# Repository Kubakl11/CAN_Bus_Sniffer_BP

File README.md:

# CAN Bus Sniffer — Bachelor Thesis - Jakub Klášterka

> **Design and Implementation of a System for CAN Bus Data Analysis in Automotive Monitoring**
>
> Czech Technical University in Prague · Faculty of Electrical Engineering · 2026

---

## About

This project implements a **complete vehicle telemetry pipeline** — from reading OBD-II data off the car's CAN bus, through cellular transmission, to a live web dashboard.

```
   Vehicle CAN Bus (500 kbit/s)
       │
       ▼  OBD-II
  ┌─────────────────────────┐
  │  ESP32-S3 + MCP2518FD   │  ← Custom 4-layer PCB
  │  + A7670E LTE/GPS       │
  └────────┬────────────────┘
           │  HTTPS (LTE)
           ▼
  ┌─────────────────────────┐
  │  Flask Backend           │  ← Railway.app
  │  (REST API + SQLite)     │
  └────────┬────────────────┘
           │  fetch() @ 5 Hz
           ▼
  ┌─────────────────────────┐
  │  Web Dashboard           │  ← Chart.js + Leaflet
  │  (Vanilla HTML/CSS/JS)   │
  └─────────────────────────┘
```

---

## Hardware

| Component | Role |
|---|---|
| **ESP32-S3-MINI-1-N8** | Main MCU (dual-core, 240 MHz) |
| **MCP2518FD** | CAN controller (SPI, CAN 2.0B @ 500 kbit/s) |
| **ATA6563** | CAN transceiver (3.3 V logic / 5 V bus) |
| **SIMCom A7670E** | LTE Cat 1 modem + GNSS (GPS/GLONASS) |

PCB designed in **KiCad**,

---

## Firmware
- **CAN library:** ACAN2517FD
- **OBD-II:** PID discovery (SCAN) + cyclic reading (LOOP) at 150 ms
- **LTE:** AT command driver for A7670E — HTTPS POST with Bearer token + nonce
- **GPS:** NMEA parsing via `AT+CGNSSINFO`
- **WiFi:** SoftAP + captive portal for local configuration

## Backend

Flask app deployed on **Railway.app**.

| Endpoint | Method | Description |
|---|---|---|
| `/data` | `POST` | ESP sends OBD-II JSON (Bearer + nonce auth) |
| `/data` | `GET` | Dashboard reads latest telemetry |
| `/command` | `POST` | Queue command for ESP (SCAN / LOOP / STOP) |

**Security:** HTTPS · Bearer token · nonce replay protection

---

## Dashboard
Written using **HTML / CSS / JavaScript**

| Page | What it shows |
|---|---|
|  `dashboard.html` | Cockpit — gauges (RPM, speed), mini charts, alarms |
|  `vehicle-data.html` | Full PID table with live values |
|  `graphs.html` | Time-series charts (Chart.js) |
|  `alarms.html` | Configurable alarm thresholds |
|  `consumption.html` | Fuel consumption analytics |
|  `map.html` | Live GPS track (Leaflet + Mapbox) |
|  `diagnostic.html` | CAN frame builder, live monitor, UDS, serial console |

**Design:** Dark theme (navy + blue accent), JetBrains Mono for numerics, responsive layout.

`data.js` serves as the **single integration point** 

---

## Quick Start

```bash
# Firmware (PlatformIO)
pio run -e obd_reader -t upload
pio device monitor

# Backend (local)
pip install -r requirements.txt
flask run

# Dashboard
# Open dashboard.html with Live Server
```

---

## 📝 Thesis

Written in **LaTeX** using the `ctuthesis` template. The thesis covers a review of automotive communication buses (CAN, LIN, FlexRay, Ethernet), the OBD-II diagnostic standard, hardware design, firmware implementation, server architecture, and the web dashboard.

---

<p align="center">
  <sub>Jakub Klášterka · CTU FEE Prague · 2026</sub>
</p>

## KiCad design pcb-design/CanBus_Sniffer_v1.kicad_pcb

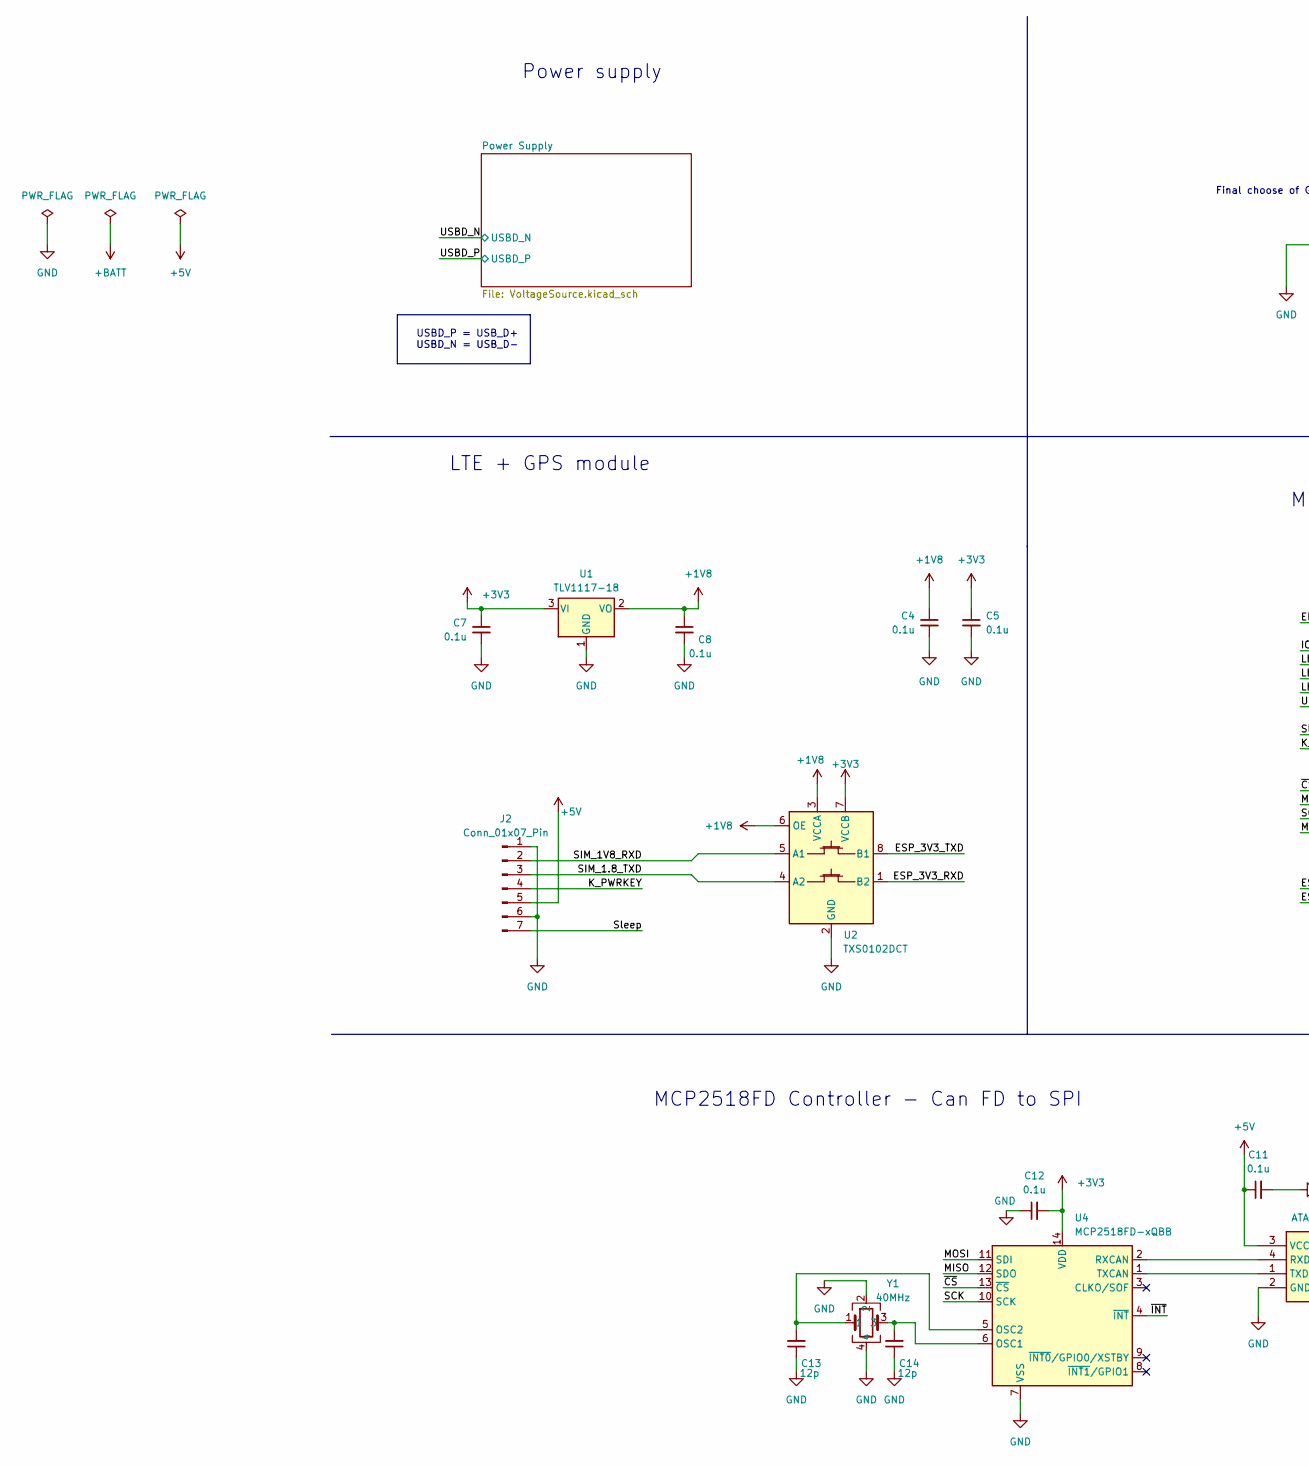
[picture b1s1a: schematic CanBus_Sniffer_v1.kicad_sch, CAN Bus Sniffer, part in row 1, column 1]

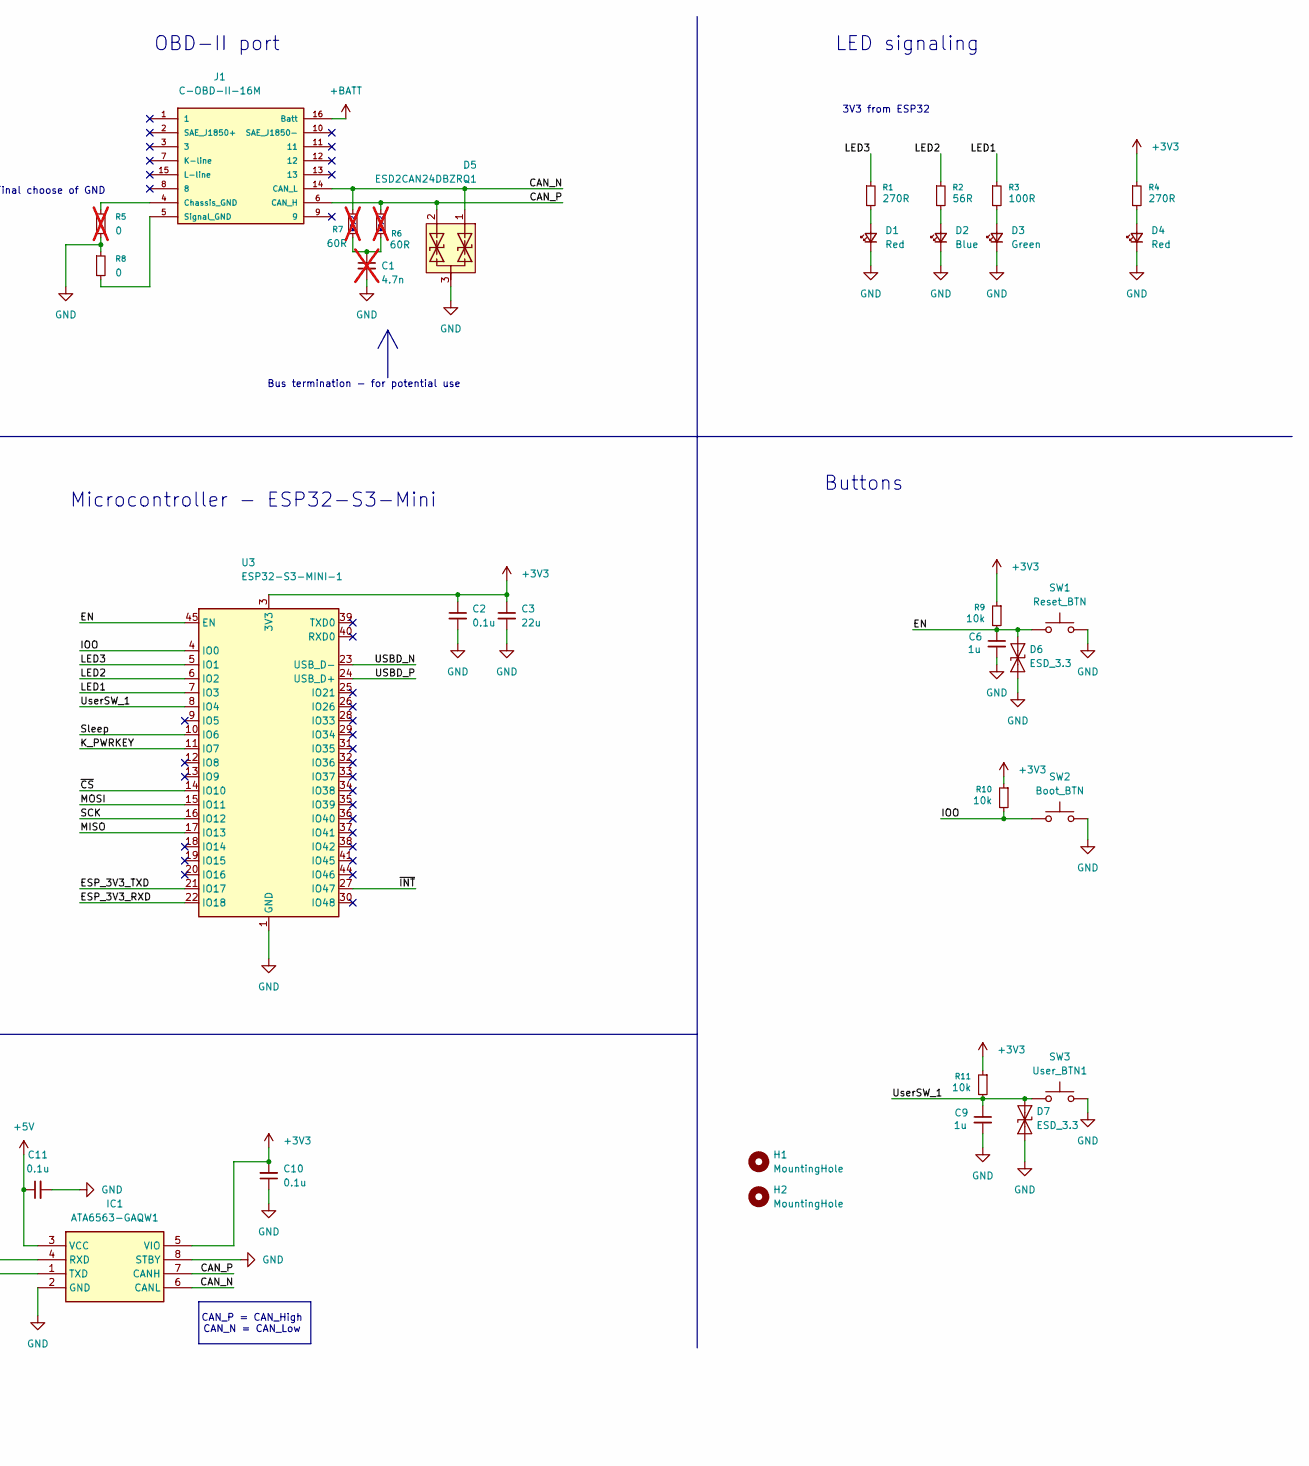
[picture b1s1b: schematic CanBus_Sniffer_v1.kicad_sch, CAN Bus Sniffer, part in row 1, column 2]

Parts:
C1: 4.7n; C_0603_1608Metric; not fitted
C2: 0.1u; C_0603_1608Metric_Pad1.08x0.95mm_HandSolder; Mouser 187-CL31B106KAHNNNE
C3: 22u; C_1206_3216Metric_Pad1.33x1.80mm_HandSolder; Mouser No 963-MSASE31LBB7226MT
C4, C5, C7, C8, C10, C11, C12: 0.1u; C_0603_1608Metric_Pad1.08x0.95mm_HandSolder; Mouser 80-C1206C104J5RAC
C6, C9: 1u; C_0603_1608Metric_Pad1.08x0.95mm_HandSolder; Mouser No 187-CL10A105KO8NNNL
C13, C14: 12p; C_0603_1608Metric_Pad1.08x0.95mm_HandSolder; Mouser 80-C1206C104J5RAC
D1, D4: Red; LED_0603_1608Metric_Pad1.05x0.95mm_HandSolder; Mouser No 710-150060RS75003
D2: Blue; LED_0603_1608Metric_Pad1.05x0.95mm_HandSolder; Mouser No 743-S63BT5B
D3: Green; LED_0603_1608Metric_Pad1.05x0.95mm_HandSolder; Mouser No 78-VLMTG1400-GS08
D5: ESD2CAN24DBZRQ1; TSOT-23; Mouser Part Number 595-ESD2CAN24DBZRQ1
D6, D7: ESD_3.3; D_SOD-323; Mouser No 621-D5V0L1B2WS-7
H1, H2: MountingHole; MountingHole_2.1mm
IC1: ATA6563-GAQW1; SOIC127P600X175-8N; Mouser Part Number 579-ATA6563-GAQW1
J1: C-OBD-II-16M; COMTECH_C-OBD-II-16M; PARTREV A
J2: Conn_01x07_Pin; PinHeader_1x07_P2.54mm_Vertical; Mouser No 737-RS1-07-G
R1, R4: 270R; R_0603_1608Metric_Pad0.98x0.95mm_HandSolder; Mouser 603-RE1206DRE071KL
R2: 56R; R_0603_1608Metric_Pad0.98x0.95mm_HandSolder; Mouser 603-RE1206DRE071KL
R3: 100R; R_0603_1608Metric_Pad0.98x0.95mm_HandSolder; Mouser 603-RE1206DRE071KL
R5: 0; R_1206_3216Metric_Pad1.30x1.75mm_HandSolder; Mouser No 71-RCS12060000Z0EA; not fitted
R6, R7: 60R; R_0603_1608Metric_Pad0.98x0.95mm_HandSolder; not fitted
R8: 0; R_1206_3216Metric_Pad1.30x1.75mm_HandSolder; Mouser No 71-RCS12060000Z0EA
R9, R10, R11: 10k; R_0603_1608Metric_Pad0.98x0.95mm_HandSolder; Mouser 603-AC1206FR-7W10KL
SW1: Reset_BTN; SW_SPST_TL1017; Mouser No 612-TL1017AAAF260QG
SW2: Boot_BTN; SW_SPST_TL1017; Mouser No 612-TL1017AAAF260QG
SW3: User_BTN1; SW_SPST_EVQP2_ShortPushTravel_H2.5mm; Mouser No 667-EVQ-PUJ02K
U1: TLV1117-18; SOT-223-3_TabPin2; Mouser No 595-TLV1117LV18DCYR
U2: TXS0102DCT; SSOP-8_2.95x2.8mm_P0.65mm; Mouser No 595-TXS0102VDCTR
U3: ESP32-S3-MINI-1; ESP32-S2-MINI-1; Mouser No 356-ESP32-S3-MINI1N8
U4: MCP2518FD-xQBB; SOIC127P600X175-14N; Mouser No 579-MCP2518FDT-E/SL
Y1: 40MHz; Crystal_SMD_2016-4Pin_2.0x1.6mm; Mouser No 815-11W40-8D1XT

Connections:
+1V8: C4.1, C8.1, U1.2 (VO), U2.3 (VCCA), U2.6 (OE)
+3V3: C2.1, C3.1, C5.1, C7.1, C10.2, C12.2, IC1.5 (VIO), R4.1, R9.1, R10.1, R11.1, U1.3 (VI), U2.7 (VCCB), U3.3 (3V3), U4.14 (VDD); also elsewhere on the board
+5V: C11.1, IC1.3 (VCC), J2.5; also elsewhere on the board
+BATT: J1.16 (Batt); also elsewhere on the board
/CAN_N: D5.1, IC1.6 (CANL), J1.14 (CAN_L), R6.1
/CAN_P: D5.2, IC1.7 (CANH), J1.6 (CAN_H), R7.1
/EN: C6.1, D6.2 (A2), R9.2, SW1.1, U3.45 (EN)
/ESP_3V3_RXD: U2.1 (B2), U3.22 (IO18)
/ESP_3V3_TXD: U2.8 (B1), U3.21 (IO17)
/IOO: R10.2, SW2.1, U3.4 (IO0)
/K_PWRKEY: J2.4, U3.11 (IO7)
/LED1: R3.1, U3.7 (IO3)
/LED2: R2.1, U3.6 (IO2)
/LED3: R1.1, U3.5 (IO1)
/MISO: U3.17 (IO13), U4.12 (SDO)
/MOSI: U3.15 (IO11), U4.11 (SDI)
/SCK: U3.16 (IO12), U4.10 (SCK)
/SIM_1.8_TXD: J2.3, U2.4 (A2)
/SIM_1V8_RXD: J2.2, U2.5 (A1)
/Sleep: J2.7, U3.10 (IO6)
/USBD_N: U3.23 (USB_D-); also elsewhere on the board
/USBD_P: U3.24 (USB_D+); also elsewhere on the board
/UserSW_1: C9.1, D7.2 (A2), R11.2, SW3.1, U3.8 (IO4)
/~CS: U3.14 (IO10), U4.13 (~CS)
/~INT: U3.27 (IO47), U4.4 (~INT)
GND: C1.2, C2.2, C3.2, C4.2, C5.2, C6.2, C7.2, C8.2, C9.2, C10.1, C11.2, C12.1, C13.1, C14.1, D1.1 (K), D2.1 (K), D3.1 (K), D4.1 (K), D5.3, D6.1 (A1), D7.1 (A1), IC1.2 (GND), IC1.8 (STBY), J2.1, J2.6, R5.2, R8.1, SW1.2, SW2.2, SW3.2, U1.1 (GND), U2.2 (GND), U3.1 (GND), U3.2 (GND), U3.42 (GND), U3.43 (GND), U3.46 (GND), U3.47 (GND), U3.48 (GND), U3.49 (GND), U3.50 (GND), U3.51 (GND), U3.52 (GND), U3.53 (GND), U3.54 (GND), U3.55 (GND), U3.56 (GND), U3.57 (GND), U3.58 (GND), U3.59 (GND), U3.60 (GND), U3.61 (GND), U3.62 (GND), U3.63 (GND), U3.64 (GND), U3.65 (GND), U4.7 (VSS), Y1.2, Y1.4; also elsewhere on the board
unnamed: C1.1, R6.2, R7.2
unnamed: D1.2 (A), R1.2
unnamed: D2.2 (A), R2.2
unnamed: D3.2 (A), R3.2
unnamed: D4.2 (A), R4.2
unnamed: IC1.4 (RXD), U4.2 (RXCAN)
unnamed: IC1.1 (TXD), U4.1 (TXCAN)
unnamed: J1.4 (Chassis_GND), R5.1
unnamed: J1.5 (Signal_GND), R8.2
unnamed: C14.2, U4.6 (OSC1), Y1.3
unnamed: C13.2, U4.5 (OSC2), Y1.1

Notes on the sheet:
RT/2
USBD_P = USB_D+ USBD_N = USB_D-
LTE + GPS module
OBD-II port
Microcontroller - ESP32-S3-Mini
3V3 from ESP32
Final choose of GND
Bus termination - for potential use
Power supply
MCP2518FD Controller - Can FD to SPI
Buttons
LED signaling
CAN_P = CAN_High CAN_N = CAN_Low

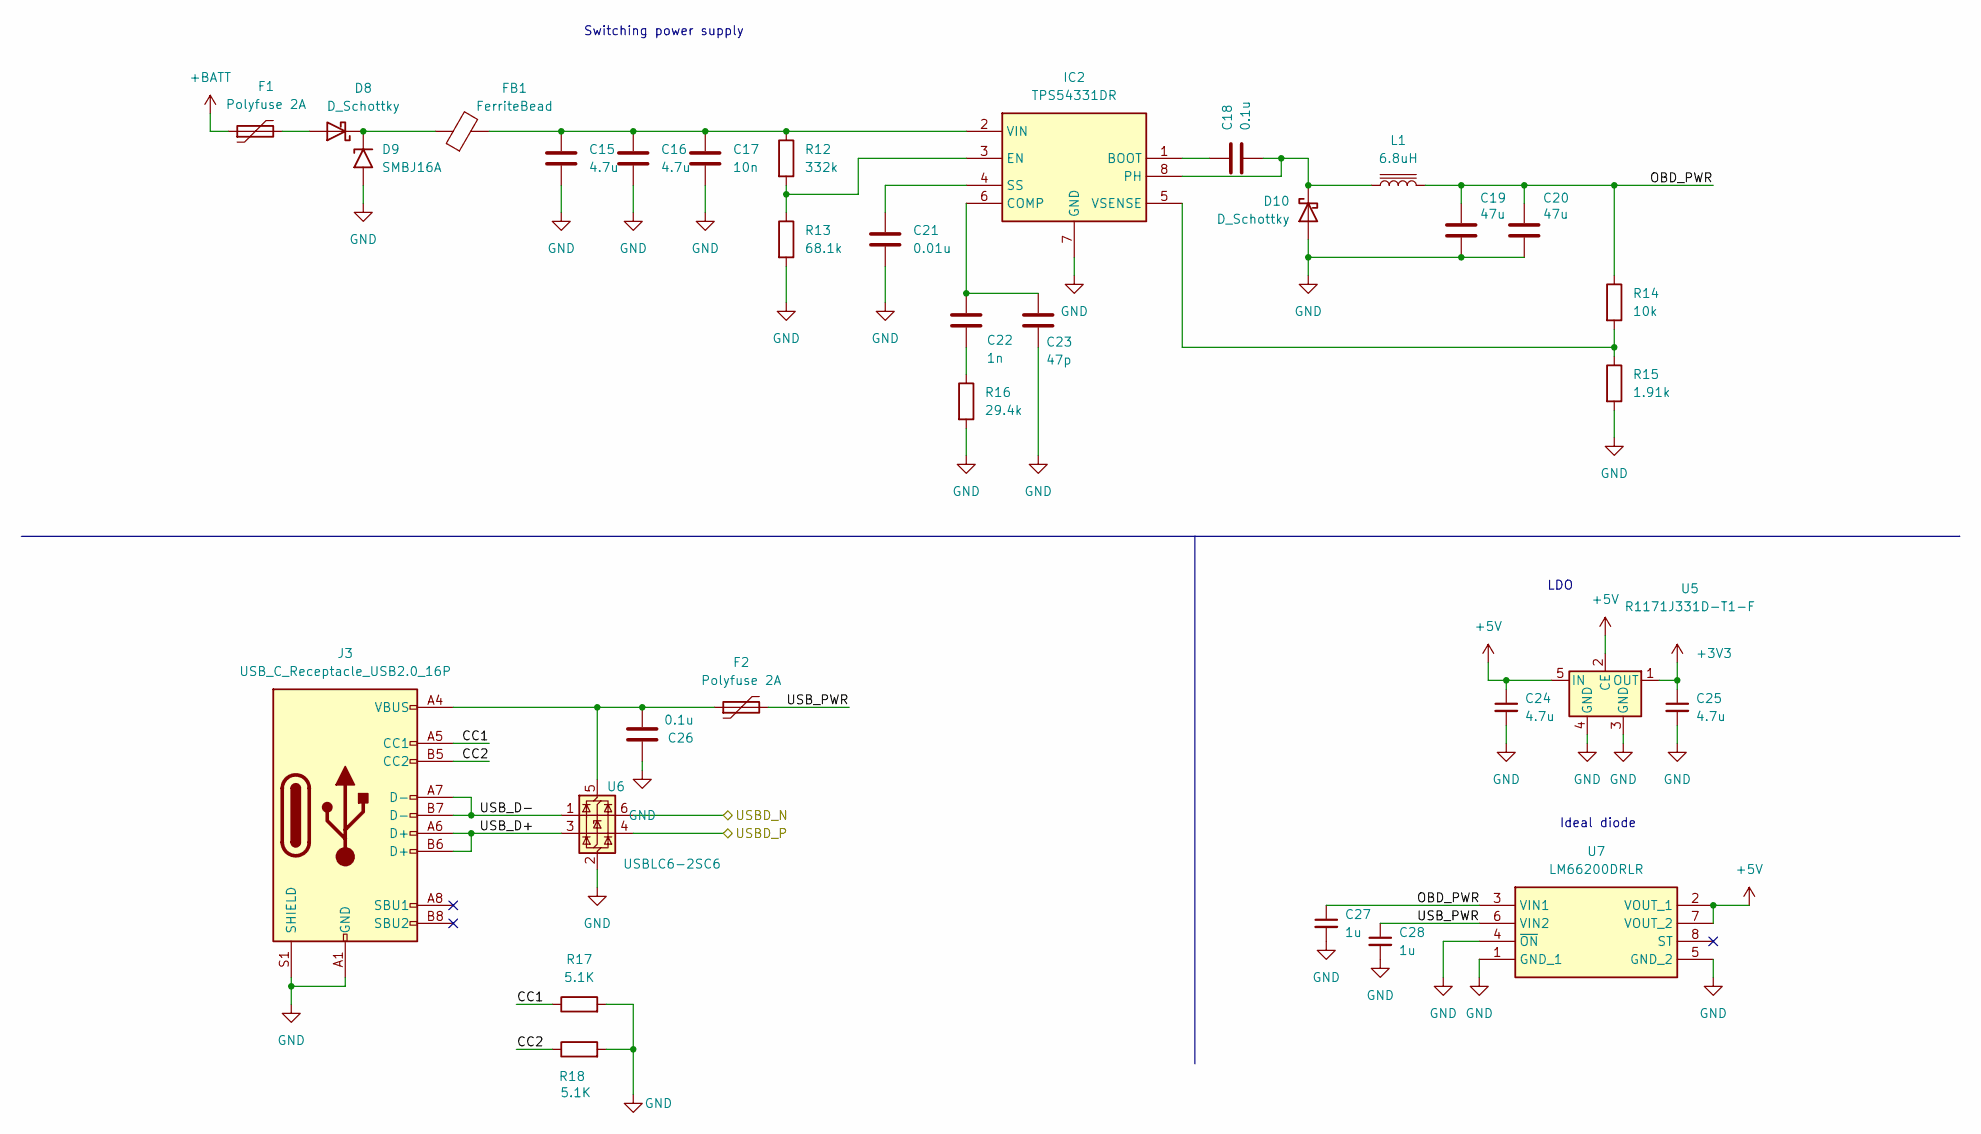
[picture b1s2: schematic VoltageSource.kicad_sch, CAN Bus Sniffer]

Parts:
C15, C16: 4.7u; R_0805_2012Metric_Pad1.20x1.40mm_HandSolder; Mouser No 810-CGA4J1X7R1H475K1
C17: 10n; C_0603_1608Metric_Pad1.08x0.95mm_HandSolder; Mouser No 810-CGA3E2X7R1H103K
C18: 0.1u; C_0603_1608Metric_Pad1.08x0.95mm_HandSolder; Mouser No 603-CC603KRX7R8BB104
C19, C20: 47u; R_1206_3216Metric_Pad1.30x1.75mm_HandSolder; Mouser No 963-MSASE31LBB5476MT
C21: 0.01u; C_0603_1608Metric_Pad1.08x0.95mm_HandSolder; Mouser No 810-CGA3E2X7R1H103K
C22: 1n; C_0603_1608Metric_Pad1.08x0.95mm_HandSolder; Mouser No 603-AC603KRX7R8BB102
C23: 47p; C_0603_1608Metric_Pad1.08x0.95mm_HandSolder; Mouser No 77-VJ0603A470JXXPBC
C24, C25: 4.7u; C_0603_1608Metric_Pad1.08x0.95mm_HandSolder; Mouser No 81-GRM188Z71C475KE1D
C26: 0.1u; C_0603_1608Metric_Pad1.08x0.95mm_HandSolder; Mouser No 810-C1608X7R1E104M
C27, C28: 1u; C_0603_1608Metric_Pad1.08x0.95mm_HandSolder; Mouser No 791-0603B105K160CT
D8: D_Schottky; D_SMA; Mouser No 750-SS54F-HF
D9: SMBJ16A; D_SMB; Mouser No 576-SMBJ16A
D10: D_Schottky; D_SMA; Mouser No 621-B340AE-13
F1: Polyfuse 2A; Fuse_1812_4532Metric_Pad1.30x3.40mm_HandSolder; Mouser No 603-SMD1812B200TF/30
F2: Polyfuse 2A; R_1210_3225Metric_Pad1.30x2.65mm_HandSolder; Mouser 576-1210L200PR
FB1: FerriteBead; L_0805_2012Metric_Pad1.05x1.20mm_HandSolder; Mouser No 81-BLM21PG121SN1D
IC2: TPS54331DR; SOIC-8-1EP_3.9x4.9mm_P1.27mm_EP2.29x3mm; Mouser Part Number 595-TPS54331DR
J3: USB_C_Receptacle_USB2.0_16P; USB_C_Receptacle_GCT_USB4105-xx-A_16P_TopMnt_Horizontal; Mouser 640-USB4105-GF-A-120
L1: 6.8uH; L_6.3x6.3_H3; Mouser No 810-VLS6045EX-6R8M
R12: 332k; R_0603_1608Metric_Pad0.98x0.95mm_HandSolder; Mouser No 667-ERJ-PA3F3323V
R13: 68.1k; R_0603_1608Metric_Pad0.98x0.95mm_HandSolder; Mouser No 755-ESR03EZPF6812
R14: 10k; R_0603_1608Metric_Pad0.98x0.95mm_HandSolder; Mouser No 71-CRCW060310K0FKEE
R15: 1.91k; R_0603_1608Metric_Pad0.98x0.95mm_HandSolder; Mouser No 71-CRCW0603-1.91K-E3
R16: 29.4k; R_0603_1608Metric_Pad0.98x0.95mm_HandSolder; Mouser No 71-CRCW060329K4FKEAH
R17, R18: 5.1K; R_0603_1608Metric_Pad0.98x0.95mm_HandSolder; Mouser 71-CRCW1206-5.1K-E3
U5: R1171J331D-T1-F; TO-252-5_TabPin3; Mouser No 848-R1171J331DT1F
U6: USBLC6-2SC6; SOT-23-6; Mouser 511-USBLC6-2SC6
U7: LM66200DRLR; SOTFL50P160X60-8N; Mouser Part Number 595-LM66200DRLR

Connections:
+3V3: C25.1, U5.1 (OUT); also elsewhere on the board
+5V: C24.1, U5.2 (CE), U5.5 (IN), U7.2 (VOUT_1), U7.7 (VOUT_2); also elsewhere on the board
+BATT: F1.1; also elsewhere on the board
/Power Supply/CC1: J3.A5 (CC1), R17.1
/Power Supply/CC2: J3.B5 (CC2), R18.1
/Power Supply/OBD_PWR: C19.1, C20.1, C27.1, L1.2, R14.1, U7.3 (VIN1)
/Power Supply/USB_D+: J3.A6 (D+), J3.B6 (D+), U6.3 (I/O2)
/Power Supply/USB_D-: J3.A7 (D-), J3.B7 (D-), U6.1 (I/O1)
/Power Supply/USB_PWR: C28.1, F2.2, U7.6 (VIN2)
/USBD_N: U6.6 (I/O1); also elsewhere on the board
/USBD_P: U6.4 (I/O2); also elsewhere on the board
GND: C15.2, C16.2, C17.2, C19.2, C20.2, C21.2, C23.2, C24.2, C25.2, C26.2, C27.2, C28.2, D9.2 (A2), D10.2 (A), IC2.7 (GND), IC2.9 (GND), J3.A1 (GND), J3.A12 (GND), J3.B1 (GND), J3.B12 (GND), J3.S1 (SHIELD), R13.2, R15.2, R16.2, R17.2, R18.2, U5.3 (GND), U5.4 (GND), U6.2 (GND), U7.1 (GND_1), U7.4 (~ON), U7.5 (GND_2); also elsewhere on the board
unnamed: C22.2, R16.1
unnamed: D8.2 (A), F1.2
unnamed: D8.1 (K), D9.1 (A1), FB1.1
unnamed: C18.1, D10.1 (K), IC2.8 (PH), L1.1
unnamed: C18.2, IC2.1 (BOOT)
unnamed: C22.1, C23.1, IC2.6 (COMP)
unnamed: IC2.3 (EN), R12.2, R13.1
unnamed: C21.1, IC2.4 (SS)
unnamed: C15.1, C16.1, C17.1, FB1.2, IC2.2 (VIN), R12.1
unnamed: IC2.5 (VSENSE), R14.2, R15.1
unnamed: C26.1, F2.1, J3.A4 (VBUS), J3.A9 (VBUS), J3.B4 (VBUS), J3.B9 (VBUS), U6.5 (VBUS)

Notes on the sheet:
Ideal diode
Switching power supply
LDO

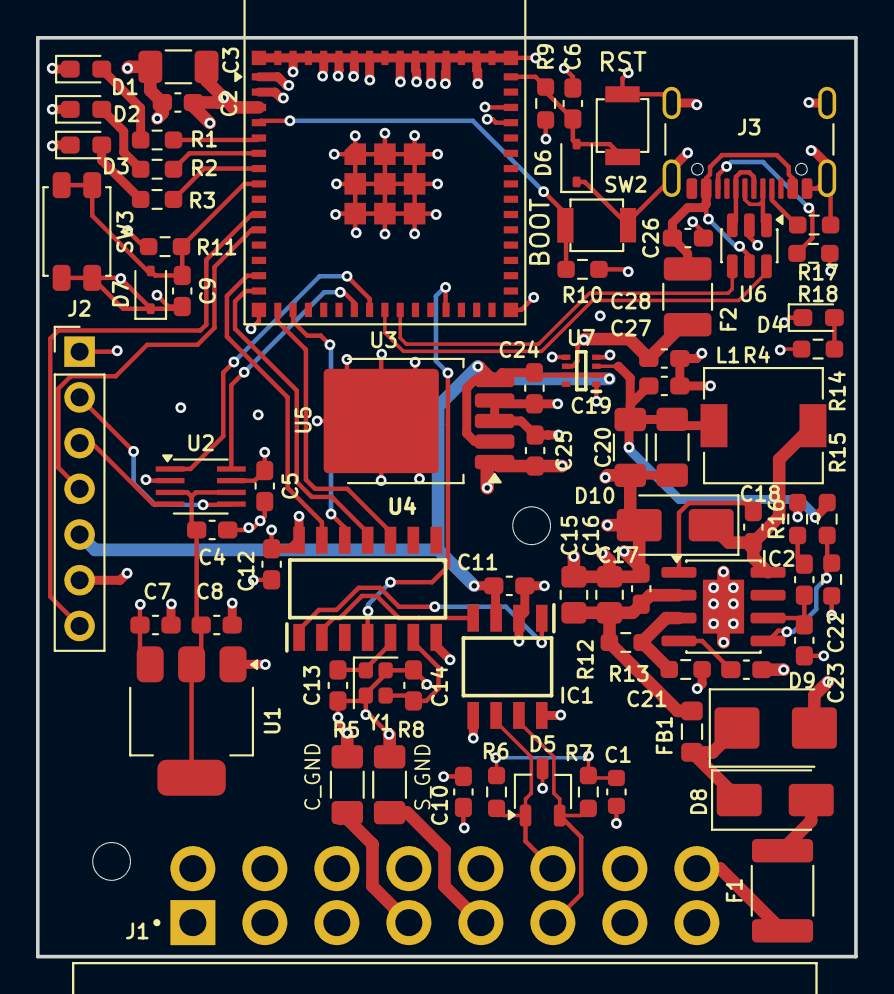
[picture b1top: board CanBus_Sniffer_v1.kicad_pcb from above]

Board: 4 copper layers, 45.5 x 51.0 mm, 78 parts (0 on the bottom side), 54 nets.

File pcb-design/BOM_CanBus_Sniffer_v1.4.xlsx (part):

Reference | Qty | Value | DNP | Exclude from BOM | Exclude from Board | Footprint | Datasheet | Mouser No | Mouser Part Number | Place | Note
Y1 | 1 | 40MHz |  |  |  | Crystal:Crystal_SMD_2016-4Pin_2.0x1.6mm | https://eu.mouser.com/datasheet/3/184/1/ABM11W.pdf | 815-11W40-8D1XT |  | YES
U7 | 1 | LM66200DRLR |  |  |  | Soucastky:SOTFL50P160X60-8N | https://www.ti.com/lit/ds/symlink/lm66200.pdf?ts=17723632276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 | 595-LM66200DRLR | 595-LM66200DRLR | YES
U6 | 1 | USBLC6-2SC6 |  |  |  | Package_TO_SOT_SMD:SOT-23-6 | https://www.st.com/resource/en/datasheet/usblc6-2.pdf | 511-USBLC6-2SC6 |  | YES
U5 | 1 | R1171J331D-T1-F |  |  |  | Package_TO_SOT_SMD:TO-252-5_TabPin3 | https://www.nisshinbo-microdevices.co.jp/en/pdf/datasheet/r1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 | 848-R1171J331DT1F |  | YES
U4 | 1 | MCP2518FD-xQBB |  |  |  | Soucastky:SOIC127P600X175-14N | https://cz.mouser.com/datasheet/3/282/1/External-CAN-FD-Cont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 | 579-MCP2518FDT-E/SL |  | YES
U3 | 1 | ESP32-S3-MINI-1 |  |  |  | RF_Module:ESP32-S2-MINI-1 | https://documentation.espressif.com/esp32-s3-mini-1_mini-1u_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 | 356-ESP32-S3-MINI1N8 |  | YES
U2 | 1 | TXS0102DCT |  |  |  | Package_SO:SSOP-8_2.95x2.8mm_P0.65mm | https://www.ti.com/lit/ds/symlink/txs0102v.pdf?ts=1771762179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 | 595-TXS0102VDCTR |  | YES
U1 | 1 | TLV1117-18 |  |  |  | Package_TO_SOT_SMD:SOT-223-3_TabPin2 | https://www.ti.com/lit/ds/symlink/tlv1117lv.pdf?ts=177181211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 | 595-TLV1117LV18DCYR |  | YES
SW3 | 1 | User_BTN1 |  |  |  | Button_Switch_SMD:SW_SPST_EVQP2_ShortPushTravel_H2.5mm | https://4donline.ihs.com/images/VipMasterIC/IC/PANA/PANA-S-A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 | 667-EVQ-PUJ02K |  | YES
SW2 | 1 | Boot_BTN |  |  |  | Button_Switch_SMD:SW_SPST_TL1017 | https://www.mouser.com/catalog/specsheets/E-Switch_TL1017.pd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 | 612-TL1017AAAF260QG |  | YES
SW1 | 1 | Reset_BTN |  |  |  | Button_Switch_SMD:SW_SPST_TL1017 | https://www.mouser.com/catalog/specsheets/E-Switch_TL1017.pd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 | 612-TL1017AAAF260QG |  | YES
R17,R18 | 2 | 5.1K |  |  |  | Resistor_SMD:R_0603_1608Metric_Pad0.98x0.95mm_HandSolder | ~ | 71-RCS06035K10FKEA |  | YES
R16 | 1 | 29.4k |  |  |  | Resistor_SMD:R_0603_1608Metric_Pad0.98x0.95mm_HandSolder | ~ | 71-CRCW060329K4FKEAH |  | YES
R15 | 1 | 1.91k |  |  |  | Resistor_SMD:R_0603_1608Metric_Pad0.98x0.95mm_HandSolder | ~ | 71-CRCW0603-1.91K-E3 |  | YES
R13 | 1 | 68.1k |  |  |  | Resistor_SMD:R_0603_1608Metric_Pad0.98x0.95mm_HandSolder | ~ | 755-ESR03EZPF6812 |  | YES
R12 | 1 | 332k |  |  |  | Resistor_SMD:R_0603_1608Metric_Pad0.98x0.95mm_HandSolder | ~ | 667-ERJ-PA3F3323V |  | YES
R9,R10,R11,R14 | 4 | 10k |  |  |  | Resistor_SMD:R_0603_1608Metric_Pad0.98x0.95mm_HandSolder | ~ | 71-CRCW060310K0FKEE |  | YES
R8 | 1 | 0R |  |  |  | Resistor_SMD:R_1206_3216Metric_Pad1.30x1.75mm_HandSolder | ~ | 71-RCS12060000Z0EA |  | YES
R6,R7 | 2 | 60R | DNP |  |  | Resistor_SMD:R_0603_1608Metric_Pad0.98x0.95mm_HandSolder | ~ | 72-P0603C60R0BNT |  | NO | Optional impedance matching
R5 | 1 | 0R | DNP |  |  | Resistor_SMD:R_1206_3216Metric_Pad1.30x1.75mm_HandSolder | ~ | 71-RCS12060000Z0EA |  | NO | Optional - Chassis GND
R3 | 1 | 100R |  |  |  | Resistor_SMD:R_0603_1608Metric_Pad0.98x0.95mm_HandSolder | ~ | 603-SR0603FR-7T100RL |  | YES
R2 | 1 | 56R |  |  |  | Resistor_SMD:R_0603_1608Metric_Pad0.98x0.95mm_HandSolder | ~ | 71-CRCW060356R0FKEAH |  | YES
R1,R4 | 2 | 270R |  |  |  | Resistor_SMD:R_0603_1608Metric_Pad0.98x0.95mm_HandSolder | ~ | 71-CRCW0603270RFKEAH |  | YES
L1 | 1 | 6.8uH |  |  |  | Inductor_SMD:L_6.3x6.3_H3 | https://product.tdk.com/system/files/dam/doc/product/inducto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 | 810-VLS6045EX-6R8M |  | YES
J3 | 1 | USB_C_Receptacle_USB2.0_16P |  |  |  | Connector_USB:USB_C_Receptacle_GCT_USB4105-xx-A_16P_TopMnt_Horizontal | https://www.mouser.com/catalog/specsheets/Global_Connector_T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 | 640-USB4105-GF-A-120 |  | YES
J2 | 1 | Conn_01x07_Pin |  |  |  | Connector_PinHeader_2.54mm:PinHeader_1x07_P2.54mm_Vertical | Headers & Wire Housings RECEPTACLE STRIP 7P 2.54MM PITCH | 737-RS1-07-G |  | YES
J1 | 1 | C-OBD-II-16M |  |  |  | Soucastky:COMTECH_C-OBD-II-16M |  |  |  | YES
IC2 | 1 | TPS54331DR |  |  |  | Package_SO:SOIC-8-1EP_3.9x4.9mm_P1.27mm_EP2.29x3mm | http://www.ti.com/lit/gpn/tps54331 | 595-TPS54331DR | 595-TPS54331DR | YES
IC1 | 1 | ATA6563-GAQW1 |  |  |  | Soucastky:SOIC127P600X175-8N | https://cz.mouser.com/datasheet/3/282/1/ATA6562.3-Data-Sheet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 | 579-ATA6563-GAQW1 | 579-ATA6563-GAQW1 | YES
H1,H2 | 2 | MountingHole |  | Excluded from BOM |  | MountingHole:MountingHole_2.1mm | ~ |  |  | YES
FB1 | 1 | FerriteBead |  |  |  | Inductor_SMD:L_0805_2012Metric_Pad1.05x1.20mm_HandSolder | https://eu.mouser.com/datasheet/3/76/1/ENFA0005.pdf | 81-BLM21PG121SN1D |  | YES
F2 | 1 | Polyfuse 2A |  |  |  | Resistor_SMD:R_1210_3225Metric_Pad1.30x2.65mm_HandSolder | https://www.littelfuse.com/assetdocs/1210l_datasheet_update.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 | 576-1210L200PR |  | YES
F1 | 1 | Polyfuse 2A |  |  |  | Fuse:Fuse_1812_4532Metric_Pad1.30x3.40mm_HandSolder | https://cz.mouser.com/datasheet/3/508/1/SMD1812_1.pdf | 603-SMD1812B200TF/30 |  | YES
D9 | 1 | SMBJ16A |  |  |  | Diode_SMD:D_SMB | https://www.littelfuse.com/assetdocs/tvs-diodes-smbj-series-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 | 576-SMBJ16A |  | YES
D8 | 1 | D_Schottky |  |  |  | Diode_SMD:D_SMA | https://cz.mouser.com/datasheet/3/819/1/20190806174558.pdf | 750-SS54F-HF |  | YES
D10 | 1 | D_Schottky |  |  |  | Diode_SMD:D_SMA | https://4donline.ihs.com/images/VipMasterIC/IC/DIOD/DIOD-S-A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 | 621-B340AE-13 |  | YES
D6,D7 | 2 | ESD_3.3 |  |  |  | Diode_SMD:D_SOD-323 | https://eu.mouser.com/datasheet/3/175/1/D5V0L1B2WS.pdf | 621-D5V0L1B2WS-7 |  | YES
D5 | 1 | ESD2CAN24DBZRQ1 |  |  |  | Package_TO_SOT_SMD:TSOT-23 | https://www.ti.com/lit/ds/symlink/esd2canxl24-q1.pdf?ts=1771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 | 595-ESD2CAN24DBZRQ1 | 595-ESD2CAN24DBZRQ1 | YES
D3 | 1 | Green |  |  |  | LED_SMD:LED_0603_1608Metric_Pad1.05x0.95mm_HandSolder | ~ | 78-VLMTG1400-GS08 |  | YES
D2 | 1 | Blue |  |  |  | LED_SMD:LED_0603_1608Metric_Pad1.05x0.95mm_HandSolder | ~ | 743-S63BT5B |  | YES
D1,D4 | 2 | Red |  |  |  | LED_SMD:LED_0603_1608Metric_Pad1.05x0.95mm_HandSolder | ~ | 710-150060RS75003 |  | YES
C24,C25 | 2 | 4.7u |  |  |  | Capacitor_SMD:C_0603_1608Metric_Pad1.08x0.95mm_HandSolder | https://pim.murata.com/asset/pim4/ceramicCapacitorSMD/GRM188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 | 81-GRM188Z71C475KE1D |  | YES
C23 | 1 | 47p |  |  |  | Capacitor_SMD:C_0603_1608Metric_Pad1.08x0.95mm_HandSolder | https://www.vishay.com/docs/28548/vjw1bcbascomseries.pdf | 77-VJ0603A470JXXPBC |  | YES
C22 | 1 | 1n |  |  |  | Capacitor_SMD:C_0603_1608Metric_Pad1.08x0.95mm_HandSolder | https://cz.mouser.com/datasheet/3/508/1/UPY-AC_NP0X7RX7S_6.3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 | 603-AC603KRX7R8BB102 |  | YES
C21 | 1 | 0.01u |  |  |  | Capacitor_SMD:C_0603_1608Metric_Pad1.08x0.95mm_HandSolder | https://product.tdk.com/system/files/dam/doc/product/capacit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 | 810-CGA3E2X7R1H103K |  | YES
C19,C20 | 2 | 47u |  |  |  | Resistor_SMD:R_1206_3216Metric_Pad1.30x1.75mm_HandSolder | https://www.mouser.com/catalog/specsheets/Tayio_Yuden_110202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 | 963-MSASE31LBB5476MT |  | YES
C17 | 1 | 10n |  |  |  | Capacitor_SMD:C_0603_1608Metric_Pad1.08x0.95mm_HandSolder | https://product.tdk.com/system/files/dam/doc/product/capacit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 | 810-CGA3E2X7R1H103K |  | YES
C15,C16 | 2 | 4.7u |  |  |  | Resistor_SMD:R_0805_2012Metric_Pad1.20x1.40mm_HandSolder | https://product.tdk.com/system/files/dam/doc/product/capacit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 | 810-CGA4J1X7R1H475K1 |  | YES
C13,C14 | 2 | 12p |  |  |  | Capacitor_SMD:C_0603_1608Metric_Pad1.08x0.95mm_HandSolder | https://datasheets.kyocera-avx.com/AutoMLCC.pdf | 581-06033A120J4T2A |  | YES
C27,C28 | 2 | 1u |  |  |  | Capacitor_SMD:C_0603_1608Metric_Pad1.08x0.95mm_HandSolder | https://cz.mouser.com/datasheet/3/317/1/WTC_MLCC_General_Pur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,~ | 791-0603B105K160CT |  | YES
C6,C9 | 2 | 1u |  |  |  | Capacitor_SMD:C_0603_1608Metric_Pad1.08x0.95mm_HandSolder |  | 187-CL10A105KO8NNNL |  | YES
C3 | 1 | 22u |  |  |  | Capacitor_SMD:C_1206_3216Metric_Pad1.33x1.80mm_HandSolder | https://www.mouser.com/catalog/specsheets/Tayio_Yuden_110202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 | 963-MSASE31LBB7226MT |  | YES
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
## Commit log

2026-06-03 CAN Bus Data Analysis System for Automotive Monitoring - repo
